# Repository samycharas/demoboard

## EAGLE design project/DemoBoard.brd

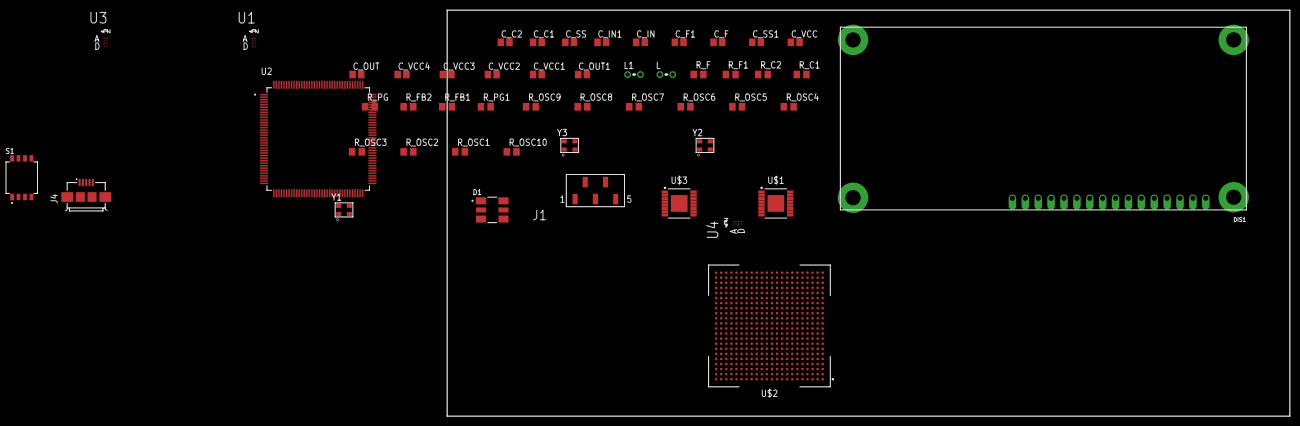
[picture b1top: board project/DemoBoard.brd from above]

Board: 2 copper layers, 166.0 x 80.0 mm, 50 parts (0 on the bottom side), 46 nets, no tracks yet.

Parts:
C_C1, C_C2: 3.3nF; C0805
C_F, C_F1: 100nF; C0805
C_IN, C_IN1: 100uF; C0805
C_OUT, C_OUT1: 100uF; C0805
C_SS, C_SS1: 33nF; C0805
C_VCC, C_VCC1, C_VCC2, C_VCC3, C_VCC4: 1uF; C0805
D1: IN-P55TATRGB; LED_IN-P55TATRGB
DIS1: HD44780_16026_16X2_BYG_5V; 16026-16X2
J1: SAMTEC-MMS-105-02-X-SVJ; SAMTEC-MMS-105-02-X-SV
J4: 10104111-0001LF; FRAMATOME_10104111-0001LF
L, L1: 1.5uH; 0204V
R_C1, R_C2: 3.16K; R0805
R_F, R_F1: 1; R0805
R_FB1: 12.7k; R0805
R_FB2: 10.2k; R0805
R_OSC1, R_OSC2, R_OSC3: 1k; R0805
R_OSC4, R_OSC6: 280; R0805
R_OSC5, R_OSC7, R_OSC8, R_OSC9, R_OSC10: 220; R0805
R_PG, R_PG1: 10K; R0805
S1: 1571983-4; SW_1571983-4
U1, U3, U4: SN74LVC2T45YZPR; BGA8C50P2X4_190X90X50
U2: STM32F207ZGT6; QFP50P2200X2200X160-144N
U$1, U$3: LM20125/LM20125Q; SOP65P640X120-17T330L
U$2: BGA352; BGA484C100P22X22_2400X2400X220N
Y1, Y2, Y3: SIT1602BI-23-18E-33.333300G; OSCDFN320X250X80-4N

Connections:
5V_EXT: C_IN.1, C_IN1.1, R_F.2, R_F1.2, R_PG.2, R_PG1.2, U$1.6, U$1.7, U$1.12, U$3.6, U$3.7
CLK: J1.4, U$2.B6
DB7: DIS1.P$14, U4.B1
GND: C_C1.2, C_C2.2, C_F.2, C_F1.2, C_IN.2, C_IN1.2, C_OUT.2, C_OUT1.2, C_SS.2, C_SS1.2, C_VCC.2, C_VCC1.2, C_VCC2.2, C_VCC3.2, C_VCC4.2, DIS1.P$1, DIS1.P$16, J4.5, R_FB2.2, U1.D1, U1.D2, U3.D1, U3.D2, U4.D1, U4.D2, U$1.5, U$1.10, U$1.11, U$1.15, U$1.16, U$1.17, U$2.A1, U$2.A4, U$2.A9, U$2.A12, U$2.A15, U$2.A19, U$2.A22, U$2.AA3, U$2.AA10, U$2.AA13, U$2.AA20, U$2.AB1, U$2.AB4, U$2.AB7, U$2.AB10, U$2.AB13, U$2.AB16, U$2.AB19, U$2.AB22, U$2.B3, U$2.B10, U$2.B11, U$2.B13, U$2.B14, U$2.C2, U$2.C3, U$2.C13, U$2.C14, U$2.C20, U$2.C21, U$2.D1, U$2.D3, U$2.D6, U$2.D9, U$2.D10, U$2.D14, U$2.D17, U$2.D18, U$2.D21, U$2.D22, U$2.E4, U$2.F4, U$2.F19, U$2.G1, U$2.G4, U$2.G19, U$2.G22, U$2.H8, U$2.H15, U$2.J4, U$2.J9, U$2.J10, U$2.J11, U$2.J12, U$2.J13, U$2.J14, U$2.K1, U$2.K4, U$2.K9, U$2.K10, U$2.K11, U$2.K12, U$2.K13, U$2.K14, U$2.K19, U$2.K22, U$2.L2, U$2.L4, U$2.L9, U$2.L10, U$2.L11, U$2.L12, U$2.L13, U$2.L14, U$2.L21, U$2.M2, U$2.M9, U$2.M10, U$2.M11, U$2.M12, U$2.M13, U$2.M14, U$2.M20, U$2.M21, U$2.N1, U$2.N4, U$2.N9, U$2.N10, U$2.N11, U$2.N12, U$2.N13, U$2.N14, U$2.N19, U$2.N22, U$2.P9, U$2.P10, U$2.P11, U$2.P12, U$2.P13, U$2.P14, U$2.R2, U$2.R8, U$2.R15, U$2.T1, U$2.T2, U$2.T19, U$2.T22, U$2.U4, U$2.U19, U$2.V4, U$2.V19, U$2.W1, U$2.W2, U$2.W6, U$2.W7, U$2.W10, U$2.W13, U$2.W16, U$2.W17, U$2.W22, U$2.Y2, U$2.Y3, U$2.Y10, U$2.Y13, U$2.Y20, U$3.5, U$3.10, U$3.11, U$3.15, U$3.16, U$3.17, Y1.2, Y2.2, Y3.2
GPIO8: R_OSC5.2, U$2.M3
GPIO9: R_OSC4.2, U$2.M4
GPIO10: R_OSC6.2, U$2.M1
GPIO12: U4.B2, U$2.Y18
GPIO20: J1.1, U$2.L22
GPIO21: J1.2, U$2.L19
GPIO22: J1.3, U$2.L20
unnamed: R_C2.2, U$3.4
unnamed: C_SS.1, U$1.1
unnamed: R_C1.2, U$1.4
unnamed: C_C1.1, R_C1.1
unnamed: C_VCC.1, U$1.13
unnamed: C_C2.1, R_C2.1
unnamed: L.2, U$1.8, U$1.9
unnamed: C_VCC1.1, U$3.13
unnamed: C_SS1.1, U$3.1
unnamed: L1.2, U$3.8, U$3.9
unnamed: C_F1.1, R_F1.1, U$3.14
unnamed: C_F.1, R_F.1, U$1.14
unnamed: S1.2, Y1.3
unnamed: C_VCC2.1, R_OSC1.2, Y1.4
unnamed: R_OSC1.1, Y1.1
unnamed: S1.3, Y2.3
unnamed: R_OSC2.2, Y2.4
unnamed: R_OSC2.1, Y2.1
unnamed: S1.4, Y3.3
unnamed: R_OSC3.2, Y3.4
unnamed: R_OSC3.1, Y3.1
unnamed: S1.2-1, S1.3-1, S1.4-1
unnamed: D1.1, R_OSC4.1
unnamed: D1.2, R_OSC5.1
unnamed: D1.3, R_OSC6.1
PG_CORE: R_PG.1, U$1.3, U$3.12
PG_IO: R_PG1.1, U$3.3
S: J4.6, J4.7, J4.8, J4.9
VCC33: D1.4, D1.6, R_OSC7.2, R_OSC10.2
VCCA: U1.A1, U3.A1, U4.A1
VCCB: U1.A2, U3.A2, U4.A2
VDD: U2.17, U2.30, U2.39, U2.52, U2.62, U2.72, U2.84, U2.95, U2.108, U2.121, U2.131, U2.144
VDD_CORE: C_OUT.1, L.1, R_FB1.2, R_FB2.1, U$1.2, U$2.C8, U$2.D4, U$2.D5, U$2.D7, U$2.D8, U$2.D15, U$2.D16, U$2.D19, U$2.E19, U$2.H9, U$2.H10, U$2.H11, U$2.H12, U$2.H13, U$2.H14, U$2.J8, U$2.J15, U$2.K8, U$2.K15, U$2.L8, U$2.L15, U$2.M8, U$2.M15, U$2.N8, U$2.N15, U$2.P8, U$2.P15, U$2.R9, U$2.R10, U$2.R11, U$2.R12, U$2.R13, U$2.R14, U$2.W4, U$2.W5, U$2.W8, U$2.W15, U$2.W18, U$2.W19, U$3.2
VDD_IO: C_OUT1.1, D1.5, L1.1, R_FB1.1, U$2.AA2, U$2.AA9, U$2.AA14, U$2.AA21, U$2.AB5, U$2.AB18, U$2.B2, U$2.B9, U$2.B12, U$2.B15, U$2.B20, U$2.B21, U$2.C4, U$2.C6, U$2.C11, U$2.C17, U$2.D20, U$2.E20, U$2.F3, U$2.F20, U$2.G3, U$2.G20, U$2.H4, U$2.H19, U$2.K2, U$2.K21, U$2.N2, U$2.N21, U$2.R4, U$2.R19, U$2.R20, U$2.T4, U$2.U3, U$2.U20, U$2.U21, U$2.V1, U$2.V21, U$2.V22, U$2.Y6, U$2.Y16, U$2.Y17
VSS: U2.16, U2.38, U2.51, U2.61, U2.83, U2.94, U2.107, U2.120, U2.130

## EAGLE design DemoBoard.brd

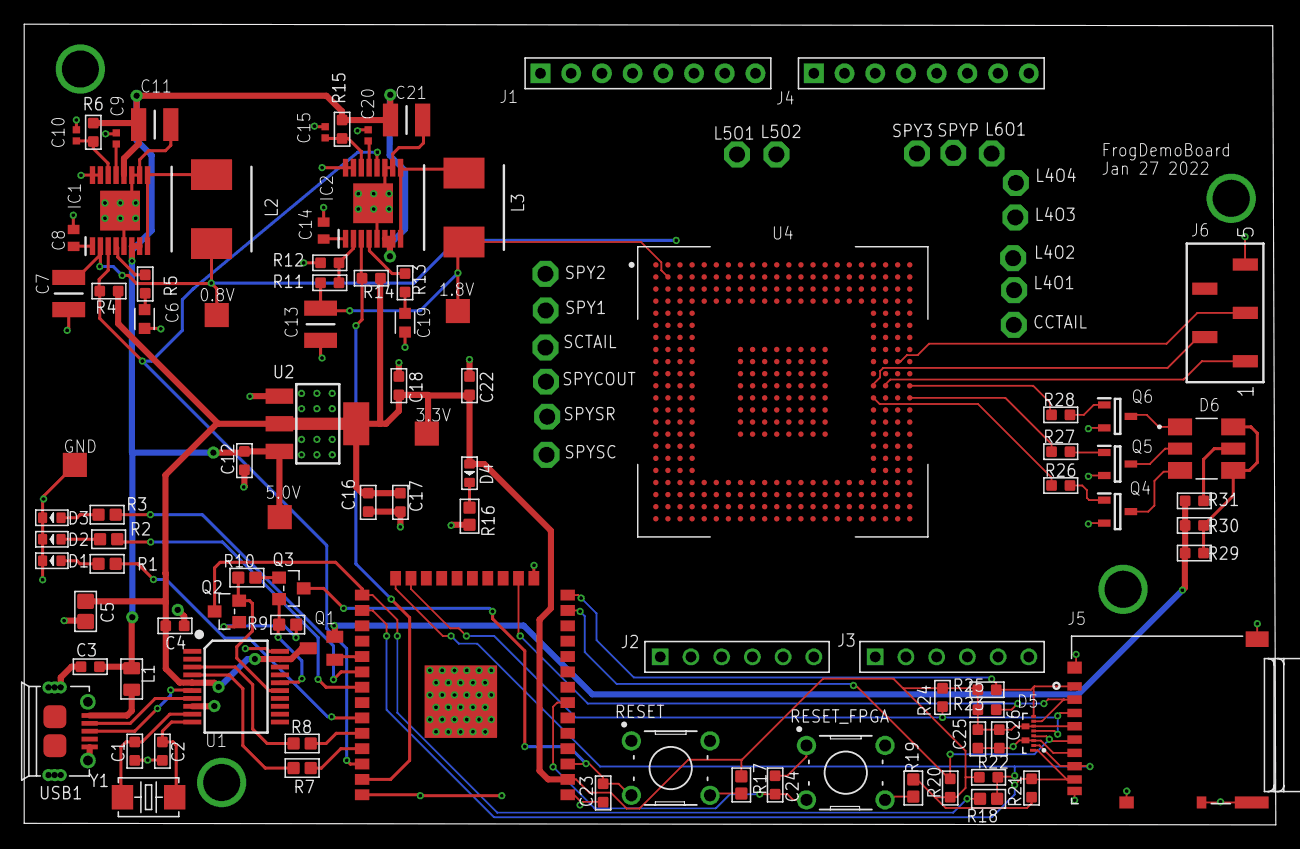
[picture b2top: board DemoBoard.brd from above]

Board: 2 copper layers, 103.5 x 66.2 mm, 109 parts (0 on the bottom side), 107 nets.

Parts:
0.8V, 1.8V, 3.3V, 5.0V: TPTP20SQ; TP20SQ
C1, C2: 22pf; C0603
C3, C12, C16, C17, C22: 10uf; C0603
C4: 100nf; C0603
C5: 22uf; C0805
C6, C19: 3.3nF; CAPC1608X85
C7, C11, C13, C21: 100uF; CAPC3225X270N
C8, C14: 33nF; CAPC1608X97N
C9, C20: 1uF; CAPC1005X55N
C10, C15: 100nF; CAPC1005X55N
C18, C23, C24, C25, C26: 1uf; C0603
CCTAIL: TPPAD1-13; P1-13
D1: RED-0603; LED-0603
D2: GREEN-0603; LED-0603
D3: BLUE-0603; LED-0603
D4: YELLOW-0603; LED-0603
D5: ESD7016MUTAG; TVS_ESD7016MUTAG
D6: IN-P55TATRGB; LED_IN-P55TATRGB
GND: TPTP20SQ; TP20SQ
IC1, IC2: LM20125MHE_NOPB; SOP65P640X120-17N
J1, J4: 8P-2.54
J2, J3: 6P-2.54-55/35MIL
J5: DM3AT-SF-PEJM5; HRS_DM3AT-SF-PEJM5
J6: SAMTEC-MMS-105-02-X-SVJ; SAMTEC-MMS-105-02-X-SV
L1: 330R-1500MA; L0805
L2, L3: 1.5uH; INDPM7066X300N
L4O1, L4O2, L4O3, L4O4, L5O1, L5O2, L6O1: TPPAD1-13; P1-13
Q1: IRLML0030TRPBF; SOT23
Q2, Q3: MMBT3904,215; SOT-23
Q4, Q5, Q6: BC846B,235; SOT95P230X110-3N
R1, R7, R8, R16: 220R; R0603
R2, R3: 100R; R0603
R4, R14: 10k; R0603
R5, R13: 3.16k; R0603
R6, R15: 1; R0603
R9, R10, R17, R19: 10K; R0603
R11: 12.7k; R0603
R12: 10.2k; R0603
R18: 0R; R0603
R20, R21, R22, R23, R25: 51K; R0603
R24: 4.7K; R0603
R26, R27, R28: 16k; R0603
R29, R30: 5.1; R0603
R31: 68; R0603
RESET: B3F-1000; SW_B3F-1000
RESET_FPGA: B3F-1000; SW_B3F-1000
SCTAIL: TPPAD1-13; P1-13
SPY1, SPY2, SPY3: TPPAD1-13; P1-13
SPYCOUT: TPPAD1-13; P1-13
SPYP: TPPAD1-13; P1-13
SPYSC: TPPAD1-13; P1-13
SPYSR: TPPAD1-13; P1-13
U1: CH340T-SSOP20; SSOP20-0.65-7.6X5.2MM
U2: PMIC-CJT1117-3.3(SOT223); SOT-223
U3: ESP32_WROOM32_SKINNY; WROOM32_SKINNY
U4: FROG12NM; BGA484C100P22X22_2400X2400X220N
USB1: ZX62-B-5PA; MICRO-USB5+6P-SMD-0.65-AB
Y1: 12MHZ - 445I33E12M00000; X2-SMD-5.0X3.2X1.3MM

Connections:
0.8V: 0.8V.TP, C7.1, IC1.2, L2.1, U4.C8, U4.D4, U4.D5, U4.D7, U4.D8, U4.D15, U4.D16, U4.D19, U4.E19, U4.H9, U4.H10, U4.H11, U4.H12, U4.H13, U4.H14, U4.J8, U4.J15, U4.K8, U4.K15, U4.L8, U4.L15, U4.M8, U4.M15, U4.N8, U4.N15, U4.P8, U4.P15, U4.R9, U4.R10, U4.R11, U4.R12, U4.R13, U4.R14, U4.W4, U4.W5, U4.W8, U4.W15, U4.W18, U4.W19
1.8V: 1.8V.TP, C13.1, L3.1, R11.1, U4.AA2, U4.AA9, U4.AA14, U4.AA21, U4.AB5, U4.AB18, U4.B2, U4.B9, U4.B12, U4.B15, U4.B20, U4.B21, U4.C4, U4.C6, U4.C11, U4.C17, U4.D20, U4.E20, U4.F3, U4.F20, U4.G3, U4.G20, U4.H4, U4.H19, U4.N2, U4.N21, U4.R4, U4.R19, U4.R20, U4.T4, U4.U3, U4.U20, U4.U21, U4.V1, U4.V21, U4.V22, U4.Y6, U4.Y16, U4.Y17
3.3V: 3.3V.TP, C4.2, C5.1, C16.2, C17.2, C18.2, C22.2, C25.2, C26.2, D4.+, D5.6, D5.9, J5.4, Q1.3, R4.1, R14.1, R17.2, R19.2, R20.2, R21.2, R22.2, R23.2, R24.2, R25.2, U1.5, U1.19, U2.2, U2.TER, U3.2
3.3VSW: Q1.2, R29.1, R30.1, R31.1
3V3_EN: Q1.1, U3.29
5.0V: 5.0V.TP, C3.2, C11.1, C12.2, C21.1, IC1.6, IC1.7, IC1.12, IC2.6, IC2.7, L1.2, R6.1, R15.1, U2.3
CCFF_HEAD: U3.6, U4.U2
CLK: J6.4, U3.12, U4.B6
DTR: Q2.2, R10.1, U1.15
GND: C1.1, C2.1, C3.1, C4.1, C5.2, C6.2, C7.2, C8.2, C9.2, C10.2, C11.2, C12.1, C13.2, C14.2, C15.2, C16.1, C17.1, C18.1, C19.2, C20.2, C21.2, C22.1, C23.1, C24.1, C25.1, C26.1, D1.-, D2.-, D3.-, D5.3, D5.10, GND.TP, IC1.5, IC1.10, IC1.11, IC1.15, IC1.16, IC1.17, IC2.5, IC2.10, IC2.11, IC2.15, IC2.16, IC2.17, J5.6, J5.P1, J5.P2, J5.P3, J5.P4, J5.SWA, J5.SWB, J6.5, Q4.2, Q5.2, Q6.2, R12.2, R16.1, RESET.1, RESET.2, RESET_FPGA.1, RESET_FPGA.2, U1.8, U1.20, U2.1, U3.1, U3.15, U3.38, U3.P$1, U4.A1, U4.A4, U4.A9, U4.A12, U4.A15, U4.A19, U4.A22, U4.AA3, U4.AA10, U4.AA13, U4.AA20, U4.AB1, U4.AB4, U4.AB7, U4.AB10, U4.AB13, U4.AB16, U4.AB19, U4.AB22, U4.B3, U4.B10, U4.B11, U4.B13, U4.B14, U4.C2, U4.C3, U4.C13, U4.C14, U4.C20, U4.C21, U4.D1, U4.D3, U4.D6, U4.D9, U4.D10, U4.D14, U4.D17, U4.D18, U4.D21, U4.D22, U4.E4, U4.F4, U4.F19, U4.G1, U4.G4, U4.G19, U4.G22, U4.H8, U4.H15, U4.J4, U4.J9, U4.J10, U4.J11, U4.J12, U4.J13, U4.J14, U4.K1, U4.K4, U4.K9, U4.K10, U4.K11, U4.K12, U4.K13, U4.K14, U4.K19, U4.K22, U4.L2, U4.L4, U4.L9, U4.L10, U4.L11, U4.L12, U4.L13, U4.L14, U4.L21, U4.M2, U4.M9, U4.M10, U4.M11, U4.M12, U4.M13, U4.M14, U4.M20, U4.M21, U4.N1, U4.N4, U4.N9, U4.N10, U4.N11, U4.N12, U4.N13, U4.N14, U4.N19, U4.N22, U4.P9, U4.P10, U4.P11, U4.P12, U4.P13, U4.P14, U4.R2, U4.R8, U4.R15, U4.T1, U4.T2, U4.T19, U4.T22, U4.U4, U4.U19, U4.V4, U4.V19, U4.W1, U4.W2, U4.W6, U4.W7, U4.W10, U4.W13, U4.W16, U4.W17, U4.W22, U4.Y2, U4.Y3, U4.Y10, U4.Y13, U4.Y20, USB1.5, USB1.P1, USB1.P2, USB1.P3_1, USB1.P3_2, USB1.P3_3, USB1.P4_1, USB1.P4_2, USB1.P4_3, USB1.P5, USB1.P6
GPIO0: J1.8, U4.A8
GPIO0_ESP: Q2.3, R18.1, U3.25
GPIO1: J4.2, U4.C10
GPIO2: J4.1, U4.C9
GPIO3: J1.5, U4.A6
GPIO4: J1.6, U4.B7
GPIO5: J1.7, U4.C7
GPIO6: J2.5, U3.8, U4.N3
GPIO7: J2.2, U3.28, U4.P1
GPIO8: J2.4, U3.9, U4.M3
GPIO9: J2.6, U3.10, U4.M4
GPIO10: J2.3, U4.M1
GPIO11: J2.1, U4.L1
GPIO12: J3.6, U4.Y18
GPIO13: J3.5, U4.AA19
GPIO14: J3.4, U4.AA18
GPIO15: J3.3, U4.AA17
GPIO16: J3.1, U4.AA16
GPIO17: J3.2, U4.AB17
GPIO18: R26.1, U4.M19
GPIO19: J4.3, J4.8, R27.1, U4.M22
GPIO20: J4.7, R28.2, U4.L22
GPIO21: J4.4, J6.2, U4.L19
GPIO22: J4.5, J6.1, U4.L20
GPIO23: J4.6, J6.3, U4.J21
unnamed: D2.+, R2.1
unnamed: R17.1, RESET.4
unnamed: R19.1, RESET_FPGA.4
unnamed: L4O4.TP, U4.E22
unnamed: L4O2.TP, U4.F21
unnamed: L4O3.TP, U4.F22
unnamed: D1.+, R1.1
unnamed: L4O1.TP, U4.G21
unnamed: L5O1.TP, U4.B4
unnamed: L5O2.TP, U4.B5
unnamed: L6O1.TP, U4.C12
unnamed: Q3.1, R10.2
unnamed: Q2.1, R9.2
unnamed: IC1.4, R5.1
unnamed: SPY2.TP, U4.P2
unnamed: SPY3.TP, U4.A10
unnamed: C6.1, R5.2
unnamed: SPY1.TP, U4.R3
unnamed: SPYCOUT.TP, U4.U1
unnamed: C9.1, IC1.13
unnamed: SPYSC.TP, U4.V3
unnamed: D3.+, R3.1
unnamed: SPYSR.TP, U4.V2
unnamed: SPYP.TP, U4.A11
unnamed: D4.-, R16.2
unnamed: U1.7, USB1.2
unnamed: U1.6, USB1.3
unnamed: C1.2, U1.9, Y1.2
unnamed: C2.2, U1.10, Y1.1
unnamed: R8.2, U1.3
unnamed: D6.1, Q6.3
unnamed: Q5.1, R27.2
unnamed: R7.2, U3.35
unnamed: C8.1, IC1.1
unnamed: IC1.8, IC1.9, L2.2
unnamed: CCTAIL.TP, U4.H22
unnamed: C10.1, IC1.14, R6.2
unnamed: IC2.4, R13.1
unnamed: C19.1, R13.2
unnamed: C20.1, IC2.13
unnamed: C14.1, IC2.1
unnamed: IC2.8, IC2.9, L3.2
unnamed: C15.1, IC2.14, R15.2
unnamed: D6.2, Q5.3
unnamed: D6.3, Q4.3
unnamed: Q6.1, R28.1
unnamed: Q4.1, R26.2
unnamed: D6.5, R31.2
unnamed: SCTAIL.TP, U4.T3
PG_CORE: IC1.3, IC2.12, R4.2, U3.36
PG_IO: IC2.3, R14.2, U3.37
PROG_CLK: U3.4, U4.AB14
P_RESET: U3.5, U4.Y14
RESET: C23.2, Q3.3, RESET.3, U3.3
RESET_FPGA: C24.2, RESET_FPGA.3, U3.7, U4.A5
RTS: Q3.2, R9.1, U1.16
RXD0: R8.1, U3.34
SC_HEAD: U3.27, U4.H20
SD_CLK_IO14: D5.4, J5.5, R20.1, U3.13
SD_CMD_IO15: D5.5, J5.3, R24.1, U3.23
SD_CS_IO13: D5.7, J5.2, R23.1, U3.16
SD_D0_IO2: D5.2, J5.7, R18.2, R22.1, U3.24
SD_D1_IO4: D5.1, J5.8, R21.1, U3.26
SD_D2_IO12: D5.8, J5.1, R25.1, U3.14
STAT_LED1: R1.2, U3.33
STAT_LED2: R2.2, U3.31
STAT_LED3: R3.2, U3.30
TEST_EN: U3.11, U4.D11
TXD0: R7.1, U1.4
VBUS: L1.1, USB1.1
VCC2: D6.4, D6.6, R29.2, R30.2
VDD_CORE: IC2.2, R11.2, R12.1

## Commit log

2020-08-26 Adding BGA lib with footprint
2022-01-27 Demoboard routing with BGA left
2022-02-07 Finalize routing, DRC Clean

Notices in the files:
parts and their libraries:
microbuilder: This work is placed in the public domain, and may be freely used for commercial and non-commercial work with the following conditions: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
